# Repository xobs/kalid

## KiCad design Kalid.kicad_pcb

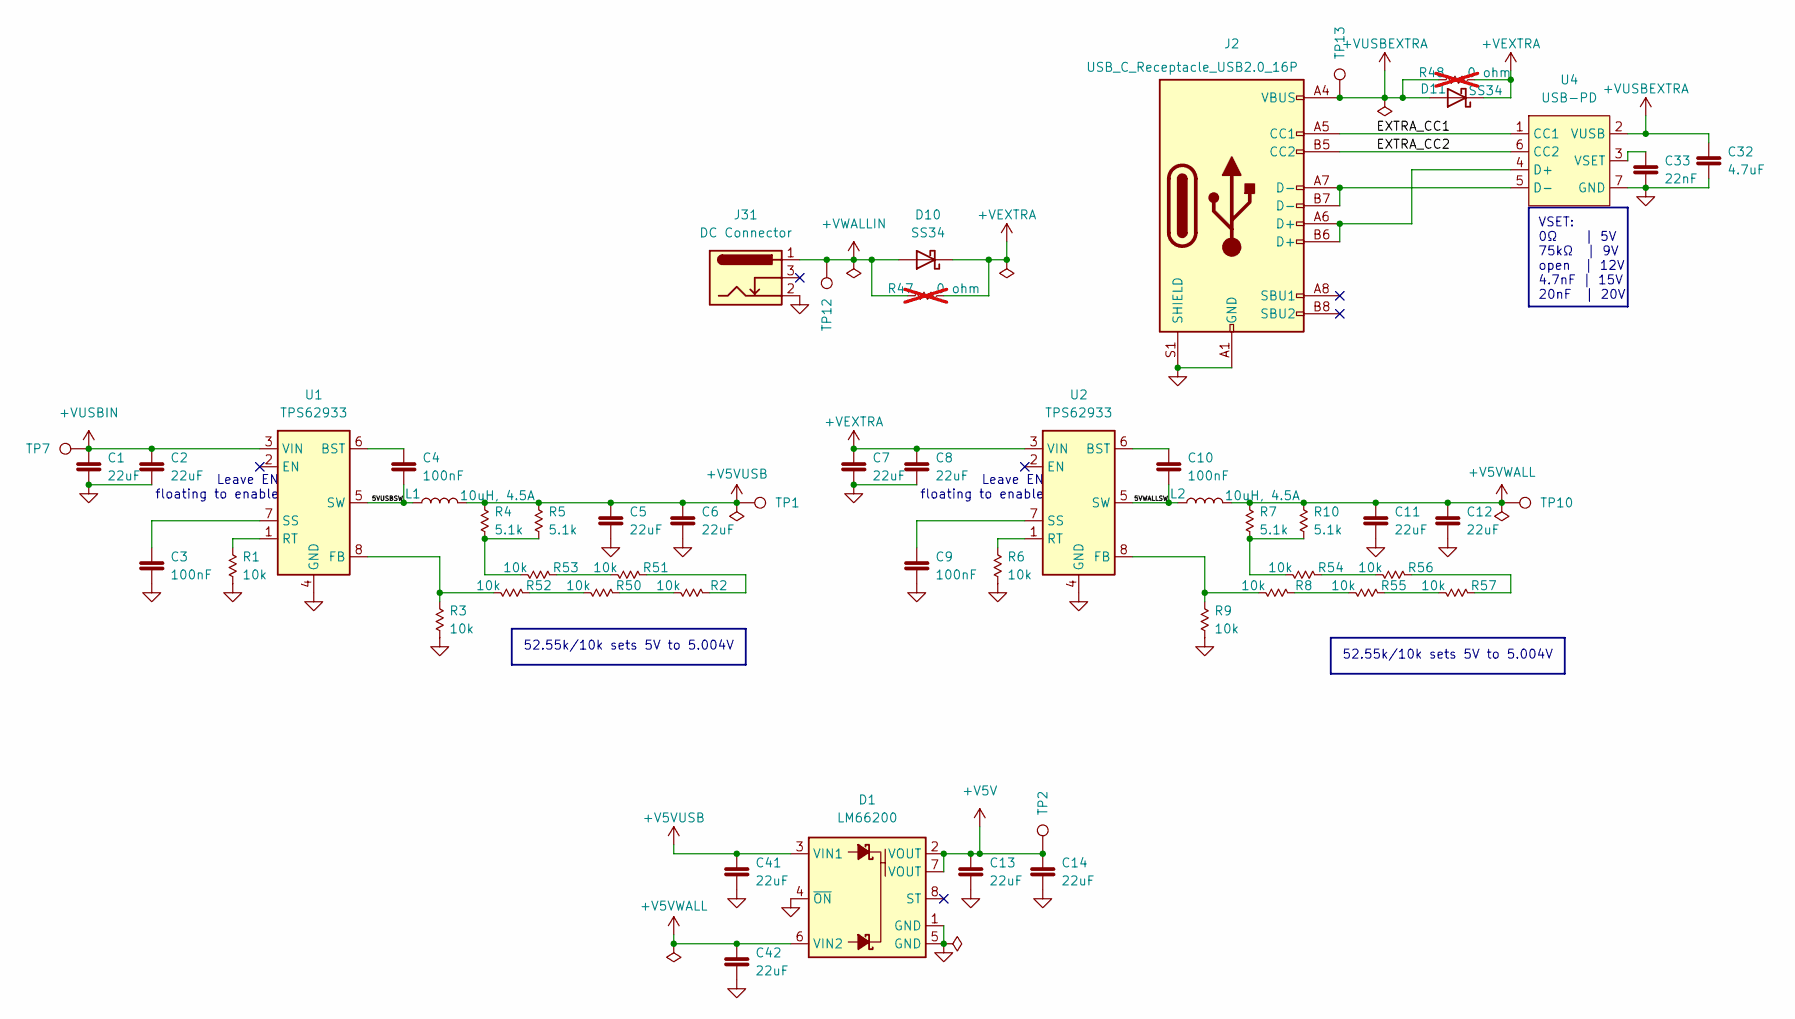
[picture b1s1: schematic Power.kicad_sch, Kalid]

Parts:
C1, C2, C5, C6, C7, C8, C11, C12, C13, C14, C41, C42: Cap 22uF; C_0805_2012Metric; MPN CL21A226MAYNNNE; LCSC C45783
C3, C4, C9, C10: Cap 100nF; C_0402_1005Metric; MPN CL05B104KB54PNC; LCSC C307331
C32: Cap 4.7uF 0402; C_0402_1005Metric; MPN 0402B472K500NT; LCSC C1538
C33: Cap 22nF 0402; C_0402_1005Metric; MPN 0402B223K500NT; LCSC C1532
D1: LM66200; SOT-583-8_L2.1-W1.2-P0.50-LS1.6-BL; MPN LM66200DRLR; LCSC C3235556
D10, D11: SS34; D_SMA
J2: USB_C_Receptacle_USB2.0_16P; USB_C_Receptacle_HRO_TYPE-C-31-M-12; MPN TYPE-C 16PIN 2MD(073); LCSC C2765186
J31: DC Connector; DC-IN-TH_DC-5520-1; MPN DC-005 2.0; LCSC C16214
L1, L2: 10uH, 4.5A; L_Changjiang_FXL0630; MPN FXL0630-100-M; LCSC C167223
R1, R2, R3, R6, R8, R9, R50, R51, R52, R53, R54, R55, R56, R57: R 10k 0402; R_0402_1005Metric; MPN 0402WGF1002TCE; LCSC C25744
R4, R5, R7, R10: R 5.1k 0402; R_0402_1005Metric; MPN 0402WGF5101TCE; LCSC C25905
R47, R48: R 0 ohm 0402; R_0402_1005Metric; MPN 0402WGF0000TCE; LCSC C17168; not fitted
TP1, TP2, TP7, TP10, TP12, TP13: TestPoint; TestPoint_Pad_D1.5mm
U1, U2: TPS62933; SOT-583-8; MPN TPS62933DRLR; LCSC C3200405
U4: USB-PD; DFN-6-1EP_2x2mm_P0.65mm_EP1x1.6mm; MPN HUSB237-AA001-DN06R; LCSC C22373734

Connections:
+V5V: C13.1, C14.1, D1.2 (VOUT), D1.7 (VOUT), TP2.1; also elsewhere on the board
+V5VUSB: C5.1, C6.1, C41.1, D1.3 (VIN1), L1.2, R4.2, R5.2, TP1.1; also elsewhere on the board
+V5VWALL: C11.1, C12.1, C42.1, D1.6 (VIN2), L2.2, R7.2, R10.2, TP10.1
+VEXTRA: C7.1, C8.1, D10.1 (K), D11.1 (K), R47.1, R48.1, U2.3 (VIN)
+VUSBEXTRA: C32.1, D11.2 (A), J2.A4 (VBUS), J2.A9 (VBUS), J2.B4 (VBUS), J2.B9 (VBUS), R48.2, TP13.1, U4.2 (VUSB)
+VUSBIN: C1.1, C2.1, TP7.1, U1.3 (VIN); also elsewhere on the board
+VWALLIN: D10.2 (A), J31.1, R47.2, TP12.1
/Hierarchy/Power/5VUSBSW: C4.2, L1.1, U1.5 (SW)
/Hierarchy/Power/5VWALLSW: C10.2, L2.1, U2.5 (SW)
/Hierarchy/Power/EXTRA_CC1: J2.A5 (CC1), U4.1 (CC1)
/Hierarchy/Power/EXTRA_CC2: J2.B5 (CC2), U4.6 (CC2)
GND: C1.2, C2.2, C3.2, C5.2, C6.2, C7.2, C8.2, C9.2, C11.2, C12.2, C13.2, C14.2, C32.2, C33.2, C41.2, C42.2, D1.1 (GND), D1.4 (~ON), D1.5 (GND), J2.A1 (GND), J2.A12 (GND), J2.B1 (GND), J2.B12 (GND), J2.S1 (SHIELD), J31.2, R1.1, R3.1, R6.1, R9.1, U1.4 (GND), U2.4 (GND), U4.7 (GND); also elsewhere on the board
unnamed: R2.1, R50.2
unnamed: R2.2, R51.2
unnamed: R4.1, R5.1, R53.1
unnamed: R7.1, R10.1, R54.1
unnamed: R50.1, R52.2
unnamed: R51.1, R53.2
unnamed: R54.2, R56.1
unnamed: R8.2, R55.1
unnamed: R55.2, R57.1
unnamed: R56.2, R57.2
unnamed: C4.1, U1.6 (BST)
unnamed: R3.2, R52.1, U1.8 (FB)
unnamed: R1.2, U1.1 (RT)
unnamed: C3.1, U1.7 (SS)
unnamed: C10.1, U2.6 (BST)
unnamed: R8.1, R9.2, U2.8 (FB)
unnamed: R6.2, U2.1 (RT)
unnamed: C9.1, U2.7 (SS)
unnamed: J2.A6 (D+), J2.B6 (D+), U4.4 (D+)
unnamed: J2.A7 (D-), J2.B7 (D-), U4.5 (D-)
unnamed: C33.1, U4.3 (VSET)

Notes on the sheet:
VSET: 0Ω | 5V 75kΩ | 9V open | 12V 4.7nF | 15V 20nF | 20V
52.55k/10k sets 5V to 5.004V
Leave EN floating to enable

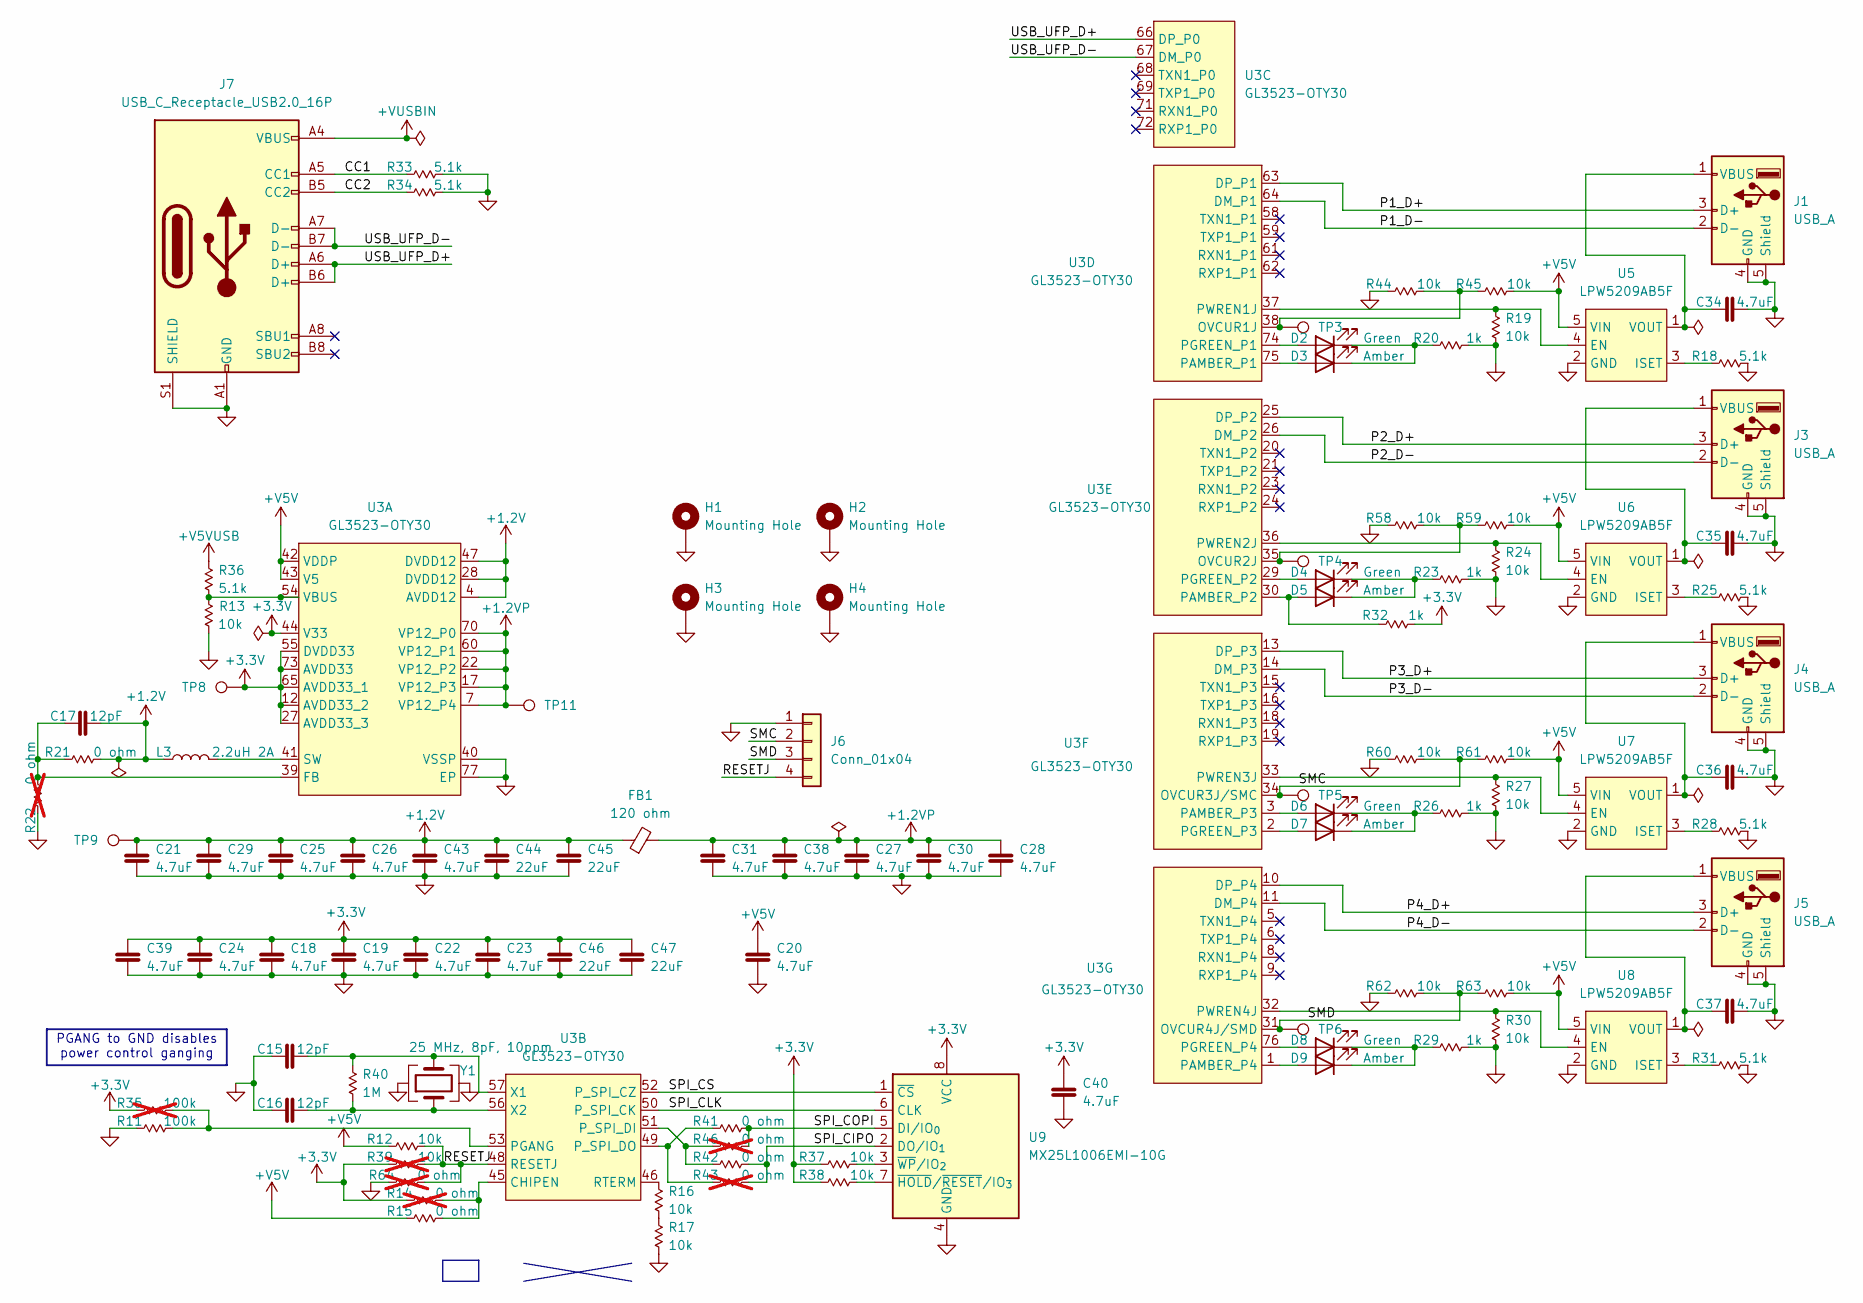
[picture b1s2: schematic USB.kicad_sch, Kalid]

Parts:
C15, C16, C17: Cap 12pF 0402; C_0402_1005Metric; MPN 0402CG120J500NT; LCSC C1547
C18, C19, C20, C21, C22, C23, C24, C25, C26, C27, C28, C29, C30, C31, C34, C35, C36, C37, C38, C39, C40, C43: Cap 4.7uF 0402; C_0402_1005Metric; MPN 0402B472K500NT; LCSC C1538
C44, C45, C46, C47: Cap 22uF; C_0805_2012Metric; MPN CL21A226MAYNNNE; LCSC C45783
D2, D4, D6, D8: Green; LED_0805_2012Metric; MPN KT-0805G; LCSC C2297
D3, D5, D7, D9: Amber; LED_0805_2012Metric; MPN KT-0805Y; LCSC C2296
FB1: 120 ohm; L_0402_1005Metric; MPN BLM15AG121SN1D; LCSC C85812
H1, H2, H3, H4: Mounting Hole; MountingHole_2.2mm_M2_DIN965_Pad_TopOnly
J1, J3, J4, J5: USB_A; USB_A_Connfly_DS1095; MPN AF 90° WJDG; LCSC C456018
J6: Conn_01x04; PinHeader_1x04_P2.54mm_Vertical; MPN PZ254V-11-04P; LCSC C2691448
J7: USB_C_Receptacle_USB2.0_16P; USB_C_Receptacle_HRO_TYPE-C-31-M-12; MPN TYPE-C 16PIN 2MD(073); LCSC C2765186
L3: L 2.2uH 2A; IND-SMD_L3.0-W3.0_LQH3NPN; MPN LVS303010-2R2M-N; LCSC C285842
R11: R 100k 0402; R_0402_1005Metric; MPN 0402WGF1003TCE; LCSC C25741
R12, R13, R16, R17, R19, R24, R27, R30, R37, R38, R44, R45, R58, R59, R60, R61, R62, R63: R 10k 0402; R_0402_1005Metric; MPN 0402WGF1002TCE; LCSC C25744
R14, R22, R43, R46, R64: R 0 ohm 0402; R_0402_1005Metric; MPN 0402WGF0000TCE; LCSC C17168; not fitted
R15, R21, R41, R42: R 0 ohm 0402; R_0402_1005Metric; MPN 0402WGF0000TCE; LCSC C17168
R18, R25, R28, R31, R33, R34, R36: R 5.1k 0402; R_0402_1005Metric; MPN 0402WGF5101TCE; LCSC C25905
R20, R23, R26, R29, R32: R 1k 0402; R_0402_1005Metric; MPN 0402WGF1001TCE; LCSC C11702
R35: R 100k 0402; R_0402_1005Metric; MPN 0402WGF1003TCE; LCSC C25741; not fitted
R39: R 10k 0402; R_0402_1005Metric; MPN 0402WGF1002TCE; LCSC C25744; not fitted
R40: R 1M 0402; R_0402_1005Metric; MPN 0402WGF1004TCE; LCSC C26083
TP3, TP4, TP5, TP6, TP8, TP9, TP11: TestPoint; TestPoint_Pad_D1.5mm
U3: GL3523-OTY30; QFN-76_L9.0-W9.0-P0.40-BL-EP; MPN GL3523-OTY30; LCSC C390630
U5, U6, U7, U8: LPW5209AB5F; SOT-23-5; MPN LPW5209AB5F; LCSC C387727
U9: MX25L1006EMI-10G; SOP-8_3.76x4.96mm_P1.27mm; MPN MX25L1006EMI-10G; LCSC C71944
Y1: Crystal 25MHz 2016; Crystal_SMD_2016-4Pin_2.0x1.6mm; MPN XL7EL89CKI-111YLC-25M; LCSC C19711739

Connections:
+1.2V: C17.2, C21.1, C25.1, C26.1, C29.1, C43.1, C44.1, C45.1, FB1.1, L3.1, R21.1, TP9.1, U3.4 (AVDD12), U3.28 (DVDD12), U3.47 (DVDD12)
+1.2VP: C27.1, C28.1, C30.1, C31.1, C38.1, FB1.2, TP11.1, U3.7 (VP12_P4), U3.17 (VP12_P3), U3.22 (VP12_P2), U3.60 (VP12_P1), U3.70 (VP12_P0)
+3.3V: C18.1, C19.1, C22.1, C23.1, C24.1, C39.1, C40.1, C46.1, C47.1, R14.2, R32.1, R35.2, R37.2, R38.2, R39.2, TP8.1, U3.12 (AVDD33_2), U3.27 (AVDD33_3), U3.44 (V33), U3.55 (DVDD33), U3.65 (AVDD33_1), U3.73 (AVDD33), U9.8 (VCC)
+V5V: C20.1, R12.2, R15.2, R45.1, R59.1, R61.1, R63.1, U3.42 (VDDP), U3.43 (V5), U5.5 (VIN), U6.5 (VIN), U7.5 (VIN), U8.5 (VIN); also elsewhere on the board
+V5VUSB: R36.2; also elsewhere on the board
+VUSBIN: J7.A4 (VBUS), J7.A9 (VBUS), J7.B4 (VBUS), J7.B9 (VBUS); also elsewhere on the board
/Hierarchy/USB/CC1: J7.A5 (CC1), R33.2
/Hierarchy/USB/CC2: J7.B5 (CC2), R34.2
/Hierarchy/USB/P1_D+: J1.3 (D+), U3.63 (DP_P1)
/Hierarchy/USB/P1_D-: J1.2 (D-), U3.64 (DM_P1)
/Hierarchy/USB/P2_D+: J3.3 (D+), U3.25 (DP_P2)
/Hierarchy/USB/P2_D-: J3.2 (D-), U3.26 (DM_P2)
/Hierarchy/USB/P3_D+: J4.3 (D+), U3.13 (DP_P3)
/Hierarchy/USB/P3_D-: J4.2 (D-), U3.14 (DM_P3)
/Hierarchy/USB/P4_D+: J5.3 (D+), U3.10 (DP_P4)
/Hierarchy/USB/P4_D-: J5.2 (D-), U3.11 (DM_P4)
/Hierarchy/USB/RESETJ: J6.4, R12.1, R39.1, R64.1, U3.48 (RESETJ)
/Hierarchy/USB/SMC: J6.2, R60.1, R61.2, TP5.1, U3.34 (OVCUR3J/SMC)
/Hierarchy/USB/SMD: J6.3, R62.1, R63.2, TP6.1, U3.31 (OVCUR4J/SMD)
/Hierarchy/USB/SPI_CIPO: R42.1, R43.1, U9.2 (DO/IO_{1})
/Hierarchy/USB/SPI_CLK: U3.50 (P_SPI_CK), U9.6 (CLK)
/Hierarchy/USB/SPI_COPI: R41.1, R46.1, U9.5 (DI/IO_{0})
/Hierarchy/USB/SPI_CS: U3.52 (P_SPI_CZ), U9.1 (~CS)
/Hierarchy/USB/USB_UFP_D+: J7.A6 (D+), J7.B6 (D+), U3.66 (DP_P0)
/Hierarchy/USB/USB_UFP_D-: J7.A7 (D-), J7.B7 (D-), U3.67 (DM_P0)
GND: C15.1, C16.1, C18.2, C19.2, C20.2, C21.2, C22.2, C23.2, C24.2, C25.2, C26.2, C27.2, C28.2, C29.2, C30.2, C31.2, C34.2, C35.2, C36.2, C37.2, C38.2, C39.2, C40.2, C43.2, C44.2, C45.2, C46.2, C47.2, H1.1, H2.1, H3.1, H4.1, J1.4 (GND), J1.5 (Shield), J3.4 (GND), J3.5 (Shield), J4.4 (GND), J4.5 (Shield), J5.4 (GND), J5.5 (Shield), J6.1, J7.A1 (GND), J7.A12 (GND), J7.B1 (GND), J7.B12 (GND), J7.S1 (SHIELD), R11.2, R13.2, R17.1, R18.1, R19.1, R20.1, R22.2, R23.1, R24.1, R25.1, R26.1, R27.1, R28.1, R29.1, R30.1, R31.1, R33.1, R34.1, R44.2, R58.2, R60.2, R62.2, R64.2, U3.40 (VSSP), U3.77 (EP), U5.2 (GND), U6.2 (GND), U7.2 (GND), U8.2 (GND), U9.4 (GND), Y1.2, Y1.4; also elsewhere on the board
unnamed: D2.2 (A), U3.74 (PGREEN_P1)
unnamed: D2.1 (K), D3.1 (K), R20.2
unnamed: D3.2 (A), U3.75 (PAMBER_P1)
unnamed: D4.2 (A), U3.29 (PGREEN_P2)
unnamed: D4.1 (K), D5.1 (K), R23.2
unnamed: D5.2 (A), R32.2, U3.30 (PAMBER_P2)
unnamed: D6.2 (A), U3.3 (PAMBER_P3)
unnamed: D6.1 (K), D7.1 (K), R26.2
unnamed: D7.2 (A), U3.2 (PGREEN_P3)
unnamed: D8.2 (A), U3.76 (PGREEN_P4)
unnamed: D8.1 (K), D9.1 (K), R29.2
unnamed: D9.2 (A), U3.1 (PAMBER_P4)
unnamed: C34.1, J1.1 (VBUS), U5.1 (VOUT)
unnamed: C35.1, J3.1 (VBUS), U6.1 (VOUT)
unnamed: C36.1, J4.1 (VBUS), U7.1 (VOUT)
unnamed: C37.1, J5.1 (VBUS), U8.1 (VOUT)
unnamed: R16.1, R17.2
unnamed: C17.1, R21.2, R22.1, U3.39 (FB)
unnamed: L3.2, U3.41 (SW)
unnamed: R13.1, R36.1, U3.54 (VBUS)
unnamed: R14.1, R15.1, U3.45 (CHIPEN)
unnamed: R11.1, R35.1, U3.53 (PGANG)
unnamed: R42.2, R46.2, U3.51 (P_SPI_DI)
unnamed: R41.2, R43.2, U3.49 (P_SPI_DO)
unnamed: R16.2, U3.46 (RTERM)
unnamed: C15.2, R40.2, U3.57 (X1), Y1.3
unnamed: C16.2, R40.1, U3.56 (X2), Y1.1
unnamed: R44.1, R45.2, TP3.1, U3.38 (OVCUR1J)
unnamed: R19.2, U3.37 (PWREN1J), U5.4 (EN)
unnamed: R58.1, R59.2, TP4.1, U3.35 (OVCUR2J)
unnamed: R24.2, U3.36 (PWREN2J), U6.4 (EN)
unnamed: R27.2, U3.33 (PWREN3J), U7.4 (EN)
unnamed: R30.2, U3.32 (PWREN4J), U8.4 (EN)
unnamed: R18.2, U5.3 (ISET)
unnamed: R25.2, U6.3 (ISET)
unnamed: R28.2, U7.3 (ISET)
unnamed: R31.2, U8.3 (ISET)
unnamed: R38.1, U9.7 (~HOLD/~RESET/IO_{3})
unnamed: R37.1, U9.3 (~WP/IO_{2})

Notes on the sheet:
PGANG to GND disables power control ganging

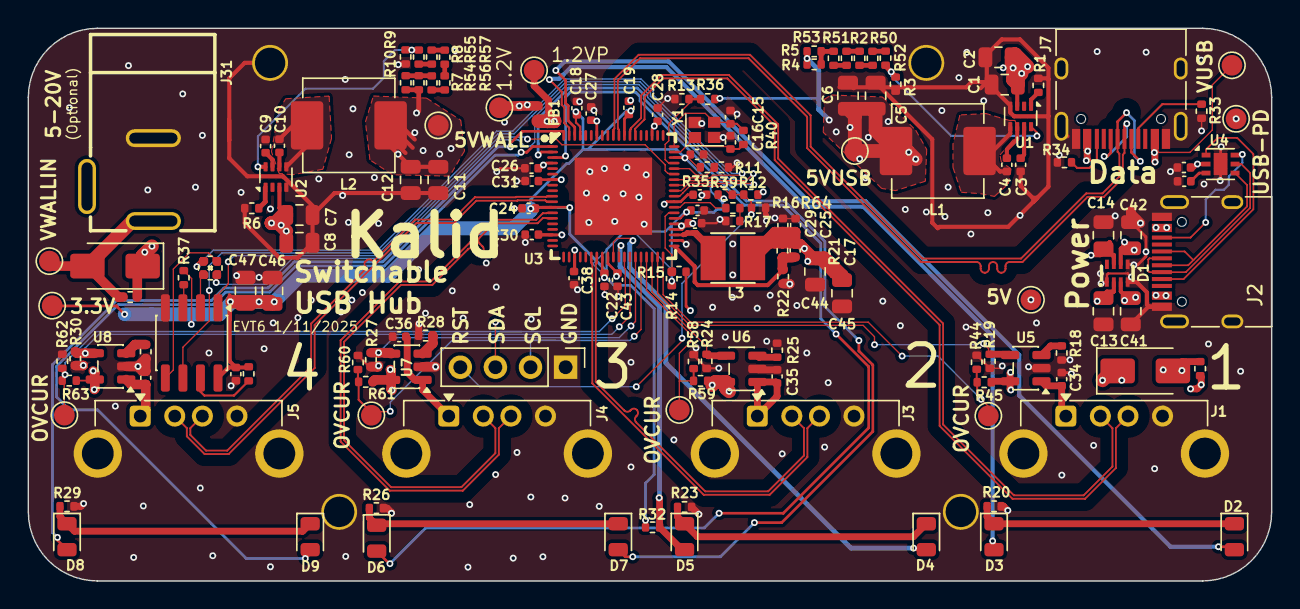
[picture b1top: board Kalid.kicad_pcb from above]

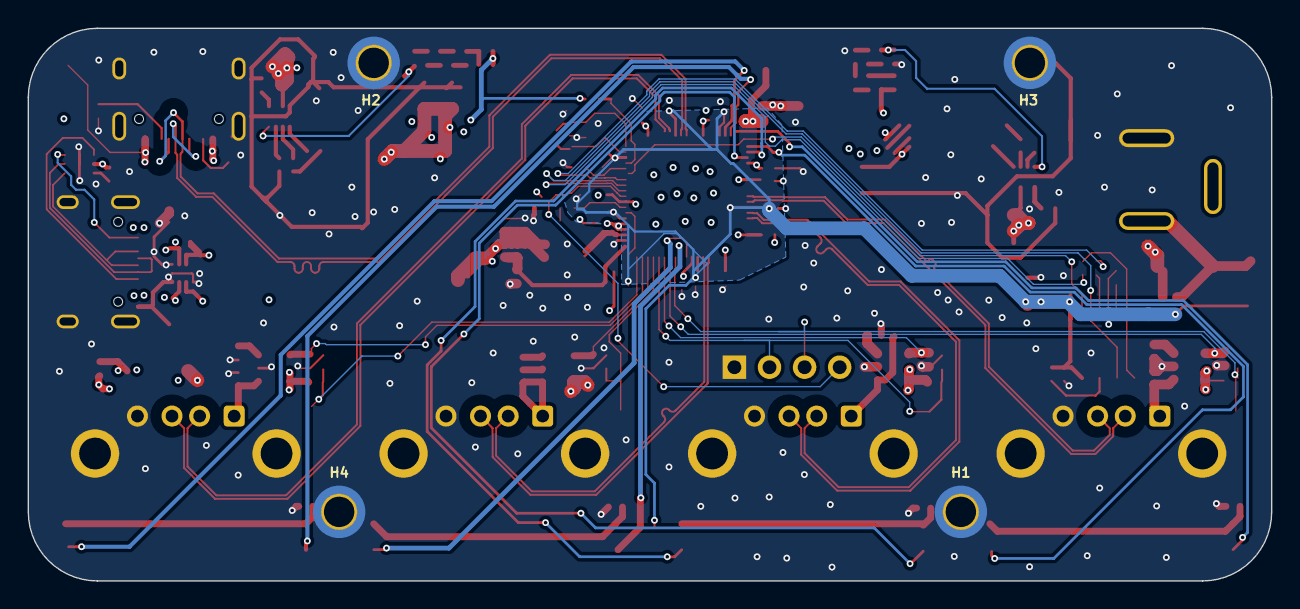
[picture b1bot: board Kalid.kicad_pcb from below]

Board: 4 copper layers, 90.0 x 40.0 mm, 160 parts (4 on the bottom side), 94 nets.

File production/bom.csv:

Designator,Footprint,Quantity,Value,LCSC Part #
"C1, C11, C12, C13, C14, C2, C41, C42, C44, C45, C46, C47, C5, C6, C7, C8",0805,16,Cap 22uF,C45783
"C10, C3, C4, C9",0402,4,Cap 100nF,C307331
"C15, C16, C17",0402,3,Cap 12pF 0402,C1547
"C18, C19, C20, C21, C22, C23, C24, C25, C26, C27, C28, C29, C30, C31, C32, C34, C35, C36, C37, C38, C39, C40, C43",0402,23,Cap 4.7uF 0402,C1538
C33,0402,1,Cap 22nF 0402,C1532
D1,SOT-583-8_L2.1-W1.2-P0.50-LS1.6-BL,1,LM66200,C3235556
"D10, D11",D_SMA,2,SS34,
"D2, D4, D6, D8",0805,4,Green,C2297
"D3, D5, D7, D9",0805,4,Amber,C2296
FB1,0402,1,120 ohm,C85812
"J1, J3, J4, J5",USB_A_Connfly_DS1095,4,USB_A,C456018
"J2, J7",USB_C_Receptacle_HRO_TYPE-C-31-M-12,2,USB_C_Receptacle_USB2.0_16P,C2765186
J31,DC-IN-TH_DC-5520-1,1,DC Connector,C16214
J6,PinHeader_1x04_P2.54mm_Vertical,1,Conn_01x04,C2691448
"L1, L2",L_Changjiang_FXL0630,2,"10uH, 4.5A",C167223
L3,IND-SMD_L3.0-W3.0_LQH3NPN,1,L 2.2uH 2A,C285842
"R1, R12, R13, R16, R17, R19, R2, R24, R27, R3, R30, R37, R38, R44, R45, R50, R51, R52, R53, R54, R55, R56, R57, R58, R59, R6, R60, R61, R62, R63, R8, R9",0402,32,R 10k 0402,C25744
"R10, R18, R25, R28, R31, R33, R34, R36, R4, R5, R7",0402,11,R 5.1k 0402,C25905
R11,0402,1,R 100k 0402,C25741
"R15, R21, R41, R42",0402,4,R 0 ohm 0402,C17168
"R20, R23, R26, R29, R32",0402,5,R 1k 0402,C11702
R40,0402,1,R 1M 0402,C26083
"TP1, TP10, TP11, TP12, TP13, TP2, TP3, TP4, TP5, TP6, TP7, TP8, TP9",TestPoint_Pad_D1.5mm,13,TestPoint,
"U1, U2",SOT-583-8,2,TPS62933,C3200405
U3,QFN-76_L9.0-W9.0-P0.40-BL-EP,1,GL3523-OTY30,C390630
U4,DFN-6-1EP_2x2mm_P0.65mm_EP1x1.6mm,1,USB-PD,C22373734
"U5, U6, U7, U8",SOT-23-5,4,LPW5209AB5F,C387727
U9,SOP-8_3.76x4.96mm_P1.27mm,1,MX25L1006EMI-10G,C71944
Y1,Crystal_SMD_2016-4Pin_2.0x1.6mm,1,Crystal 25MHz 2016,C19711739

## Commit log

2025-07-25 Start layout
2025-07-28 initial routing
2025-07-28 finish routing
2025-07-28 name the project
2025-07-28 generate evt1 production
2025-08-06 manufacture evt1
2025-08-06 fix 90-ohm trace width
2025-08-18 add t113
2025-08-18 add testpoint
2025-08-18 develop evt2
2025-08-18 release evt2
2025-08-18 tag schematic and pcb as evt2
2025-08-29 evt3
2025-09-04 evt4 - route usb3 lines
2025-09-18 release evt5
2025-11-06 add second power circuit
2025-11-09 evt5: Release
2026-05-09 case: initial commit
